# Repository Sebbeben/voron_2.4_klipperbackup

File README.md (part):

# voron_2.4_klipperbackup

Klipper configuration backup for my Voron 2.4 350 (pushed automatically by [Klipper-backup](https://github.com/Staubgeborener/Klipper-Backup)).

## Hardware
- [Fysetc Voron 2.4 kit 350](https://github.com/FYSETC/FYSETC-Voron-2) (shipped with Spider v1.1 and Omron SSR, i.e. [BOM](https://github.com/FYSETC/FYSETC-Voron-2/blob/main/BOM.md) rev 1.3 / R2 rev 1.0)
  - XY + Z motors: 6x [17HS19-2004S-C](https://github.com/FYSETC/FYSETC-MOTORS/tree/main/17HS19-2004S-C) (2.0 A), run at 0.8 A
  - Bed heater: 300x300 silicone AC heater, 750 W, with thermal fuse RH15A125
- [Fysetc Aluminium parts kit](https://github.com/FYSETC/FYSETC-VORON-2.4-R2-Pro/tree/main/2.4%20R2%20CNC%20V2.0/2.4%20R2%20CNC%20V2.0)
- Raspberry Pi 4B 8GB
  - [Waveshare RS485 CAN HAT](https://www.waveshare.com/wiki/RS485_CAN_HAT) (MCP2515 over SPI, `oscillator=12000000, interrupt=25, spimaxfrequency=10000000` in `/boot/config.txt`)
- [Fysetc Spider v1.1](https://github.com/FYSETC/FYSETC-SPIDER) (connected to the Pi over UART `/dev/ttyAMA0`)
  - [Fysetc TMC2209 v3.1](https://github.com/FYSETC/FYSETC-TMC2209) ([Silent2209](https://fysetc.github.io/Silent2209/))
  - [Fysetc Canbus Expander for Spider](https://github.com/FYSETC/FYSETC-SPIDER/blob/main/images/CANBUS.jpg)
- [Mellow SB2040 v1](https://mellow-3d.github.io/fly_sb2040_v1_general.html#fly-sb2040-v1-overview) (CAN, 1 Mbit) - [pin definitions](https://mellow-3d.github.io/fly_sb2040_v1_pins.html)
- Orbiter extruder (version to be verified - `rotation_distance: 4.637` is the Orbiter 2.0 value)
  - [FYSETC G36HSY4405-6D-1200 stepper motor](https://github.com/FYSETC/FYSETC-MOTORS/blob/main/G36HSY4405-6D-1200/G36HSY4405-6D-1200.pdf), run at 0.65 A
- [Rapido UHF Hotend](https://www.phaetus.com/products/rapido-hotend?variant=45122834465045) (v1, HF + UHF nozzles included)
  - Currently: temporary V6 0.4 mm nozzle; plan: HF nozzle back, then UHF with a new toolhead
- [BTT Pi Screen 5"](https://github.com/bigtreetech/BIGTREETECH-TouchScreenHardware/tree/master/BTT%20Pi%20TFT50%20V2.0%20Github/Hardware)
- [BIQU CNC Voron Tap V2](https://github.com/Chaoticlab/CNC-Tap-for-Voron/tree/master/STL/CNC_VORON_TAP_V2) on SB2040 `gpio28` (replaced the Chaotic Labs Tap V2.0 / OptoTap v2.1). 2026-11-17: `PROBE_ACCURACY` stddev 0.0009 mm, range 0.0038 mm; `z_offset` -0.896
- X rail upgraded to MGN12H (needed for CNC Tap V2); Y and Z still original MGN9 (no grease ports). Greased with Mobilux EP 2
- CNC Aluminium Idlers
- [Meanwell LRS-200-24 psu](https://meanwell-ps.com/products/lrs-200-24)
- [Voron Daylight on a stick XXL](https://github.com/VoronDesign/Voron-Hardware/tree/master/Daylight) (`output_pin daylight`, PB15)
- Pi Cam (OV5647, 1280x720 @ 15 fps via Crowsnest)
- USB camera YJXU502S (Realtek RTS58xx, 0edc:2050), 1920x1080 @ 15 fps, Crowsnest `[cam 2]` ustreamer port 8081, Mainsail "USB Cam". The on-board LED is not controllable over USB (do not write to the UVC extension unit)
- Voron 2.4 silicone nozzle brush at the rear of the bed - KOMB area X 60.5-93.5, Y 347.5-350.0, Z 3.5 (Y 350.5 touches the frame)
- [Nevermore Duo](https://github.com/nevermore3d) under the bed (M3 T-nuts in the bed extrusion), 2 blowers in parallel on Spider FAN0 (`PB0`) as `[fan_generic nevermore]`. On in `PRINT_START` when bed > 90 C, off 10 min after `PRINT_END`
- ADXL345 accelerometer (loose, mounted on the toolhead only for calibration) wired to the Pi SPI0 bus, **CS on CE1 = pin 26 / GPIO7** (CE0 = pin 24 belongs to the MCP2515 CAN HAT - CS there kills CAN). Pi runs `klipper-mcu` as `[mcu rpi]`, `[adxl345] spi_bus: spidev0.1`, `axes_map: -z,-y,-x`
- Chamber air: 3 x NTC 100K (temporary test positions, Spider TE0/TE1/TE2 = PC0/PC1/PC2), `chamber_sensors.cfg`. Z `position_max` temporarily 200 while they hang under the top panel (restore 340)
- Gantry NTC (2026-11-25): a 4th NTC 100K pulled through the Z drag chain together with the new A/B motor cables, **not connected yet**. Plan: chamber air sensor on top of the gantry extrusion (moves with Z, so it reads the air at the gantry, which is what drives QGL/gantry drift). All Spider thermistor inputs are taken (PC0/PC1/PC2 chamber, PC3 bed), so it replaces one of the test sensors (`chamber_side` PC1 is the obvious one). Mounting: middle of the gantry, >= 100 mm from the A/B motors (they warm the aluminium), bead 10-20 mm above the extrusion in free air, not touching metal (printed standoff), outside the part-fan / Nevermore airflow. Expect it to read high at low Z (bed radiation) - only trust it for heatsoak at print height
- [OMRON G3NB-225B-1 25A SSR](https://www.omron-ap.com/products/family/3232/download/catalog.html)

### Fans
| Position | Fan | Pin | Status |
|---|---|---|---|
| Hotend (lower, 4010 axial) | [HoneyBadger 4010A-24-9400 "High SP & Tach"](https://3do.dk/en/fans/1145-4010-axial-fan-24v-by-honeybadger-high-sp-9400-rpm.html), 3-wire, not PWM | SB2040 fan adapter "Hotend Fan1": red -> 24V, black -> AGND (switched GND, `gpio14`); white tach **not connected** yet | **Installed 2026-11-17**, tested: on at 50 C, off below 50 C |
| Part cooling (upper, 5015 blower) | [HoneyBadger 5015 blower 9200 RPM, 4-wire PWM/tach, wide mouth](https://3do.dk/en/fans/4366-5015-blower-fan-by-honeybadger-9200-rpm-4-wires-pwmtach-wide-mouth.html) | SB2040 power `gpio13`, PWM `gpio17` | Ordered 2026-11-13 - duct needs adapting for the wide mouth |
| Electronics bay | Kit 6020 fans | Spider `PB2` (on when bed > 45 C) | Check that they still spin |
| Nevermore Duo | 2 x blower | Spider FAN0 `PB0` | Installed 2026-11-17 |

Hotend fan config: `printer.cfg` `[heater_fan hotend_fan]` (wiring in the comments). Stall watchdog: `hotend_fan_alarm.cfg` (included, idle until the tach is wired; plan 2026-11-25: tach -> SB2040 ENDSTOP_2 `gpio25`).

**Hotend fan wiring notes (learned the hard way, 2026-11-17):**
- On the Mellow fan adapter, "AGND" is the *switched* fan ground (low-side MOSFET), not analog ground. 2-wire / non-PWM fans go 24V + AGND.
- The adapter's "3 Line: S = PWM" row is for PWM fans only. A tach wire must **never** go to PWM0/PWM1: with the white tach on PWM0 (`gpio16`) the SB2040 MCU temperature read 120-135 C and Klipper shut down.
- The adapter has no tach input. SB2040 v1 inputs (schematic REV 1.0): ENDSTOP_0 `gpio28` (JP9, 4.7k pull-up to 3V3, Tap), ENDSTOP_1 `gpio29` (JP10, 4.7k pull-up, reserved for the X endstop), ENDSTOP_2 `gpio25` (JP11: 1 = signal, 2 = GND, 3 = **24 V**; input through a 1N4148 cathode-to-connector + 1k, 100 nF on the connector side, no pull-up -> 24 V tolerant, pulls low only). Status LED is `gpio24`, not 25.
- Tach plan: white wire -> JP11 pin 1, nothing on pin 3, `tachometer_pin: ^SB2040:gpio25`. First measure the white wire with the fan running and unconnected: if it shows a voltage the fan has its own pull-up and it works directly; if ~0 V add a 10k pull-up from the tach line to JP11 pin 3 (24 V), because the 100 nF + internal ~50k pull-up through the diode is too slow for ~310 Hz.

The part fan (5015) config is still prepared (commented out) in `fan_upgrade.cfg`.

## Hardware *Not installed*
- Mellow 3 m shielded twisted-pair CAN cable (20CANW3M) - plan: replace the current CAN cable
- FYSETC belt tension gauge (tool)
- Spare Orbiter motor: FYSETC 36STH20-1004AHG
- Simple filament runout switch
- Voron PT100 Stick
- Fysetc CNC Aluminium Clockwork extruder
- Unused kit parts: BMG extruder kit + 42HS20401B motor, E3D V6 hotend

## Klipper Mods
- [Klipper-backup](https://github.com/Staubgeborener/Klipper-Backup)
- [Klipper-Adaptive-Meshing-Purging (KAMP)](https://github.com/kyleisah/Klipper-Adaptive-Meshing-Purging) - Smart_Park is used in `PRINT_START`
- [KOMB](https://github.com/TmRxJD/KOMB) nozzle brushing macro - **enabled 2026-11-17**. Local patch in `KOMB/KOMB.cfg`: travel to the brush at z_hop height *before* lowering (upstream lowers first and crosses the bed at brush height)
- [Filament dryer macro](https://gist.github.com/NameOfTheDragon/e579295549aaa19b3f41ae07b8f3cbd6#file-filament_dryer-cfg) - `DRY_ABS` = bed 95 C for 5 h (spool on a spacer, door slightly open)
- Crowsnest, Moonraker-timelapse, Sonar, KlipperScreen

## Printed Mods
- [Orbitu for Stealthburner Orbiter extruder](https://github.com/Saccco/VoronUsers/tree/master/printer_mods/Saccco/Orbitu)
- Planned: [Voron Stealthburner Rapido UHF](https://www.printables.com/model/1272320-voron-stealthburner-rapido-uhf) (4010 hotend fan version)

## Maintenance log

### 2026-11-27 - extruder grip fixed, R3D ABS calibrated, USB cam CPU lowered
- Max-flow walls failed at ~15 mm3/s -> in-air feed test (100 mm per step, tape mark): Orbiter tension far too loose (16 mm3/s fed 88 %, 20 fed 77 %). Tightened in quarter turns: 20 -> 97 %, 24 -> 94 %, 28 -> motor skips at 250 C, 88 % without skipping at 260 C
- `rotation_distance` 4.544 -> **4.703** (4.544 fed 103.5 mm after the tension fix; re-check fed exactly 100 mm)
- Second calibration plate (all tests on one plate, `plate_20261127.gcode`), judged with a microscope: flow ratio **0.99**, PA **0.045** kept, **250 C**, retraction **0.5 mm**, max volumetric **18 mm3/s** (22 at 260 C). Values in `orca_profiles/ABS @...json` + `orca_profiles/README.md`; best photos in `~/calibration/` on the Pi
- Remaining fine wisps on travel are the same at 0.4 and 1.2 mm retraction -> dry the filament (`DRY_ABS`)
- USB cam WebRTC (go2rtc, with audio) encode 960x540 @ 15 -> 640x360 @ 10 fps: encoder ~78 % -> ~44 % of a core while watched. Full-res snapshot unchanged

### 2026-11-18 - A/B motor fault hunt, motors ordered, camera sound in Mainsail
- Sensorless homing `uv_cp` fault traced step by step to **motor B** (supply, driver modules, X-MOT socket, both cables and endstop ports ruled out - details in TODO "A/B motor fault"). Motor A cable was also bad (open-load flags) and was replaced
- `homing_v2.cfg`: `G4 P2000` before sensorless `G28 X`/`G28 Y` (Klipper TMC docs); X/Y `homing_speed` back to 80
- Ordered 2 x LDO-42STH48-2504AC + 2 x adhesive heatsinks (3do.dk). Printer parked until they arrive; X-MOT/Y-MOT plugs and pins are temporarily swapped
- Driver/motor research: Spider v1.1 is 24 V only (35 V caps); TMC2240 (SPI, StallGuard4) is the next driver step; LDO "Super Power" 2804 only pays off with 48 V; no vibration dampers on A/B
- Chamber heater research (PTC 300-500 W, ~80 C practical limit, PA/PC possible, PEEK/PEI not) - TODO "Chamber heater"
- USB camera sound: go2rtc v1.9.14 installed as a service, nginx proxy `/go2rtc/`, Mainsail webcam "USB Cam + ljud" (WebRTC go2rtc, audio). Video via software x264 960x540 (the Pi hardware encoder only sent SPS/PPS once). Mic gain +12 dB (saved). Mainsail player patched (`printer_data/config/system/mainsail_go2rtc_audio_patch.sh`, re-run after Mainsail updates) - Mainsail kept re-muting the video and had no controls. Old MJPEG "USB Cam" entry removed. Sound verified on another PC (not yet on the main PC - local browser/PC issue)
- Camera LED: still no software control found (only Realtek raw-register XU 4, not touched). Connector has 5 pins - the extra pin is the next thing to check; seller asked

### 2026-11-17 - On site: homing, Tap, brush, Nevermore, input shaper, hotend fan
- `G28 X` shut down with `TMC stepper_x GSTAT uv_cp=1` (charge-pump undervoltage). Homing "finished" instantly (driver fault raises DIAG = fake stall). **Cause: loose 24 V cable** - re-tightened, homing fine since. If `uv_cp` comes back, check the 24 V terminals first.
- `homing_v2.cfg` enabled (fixed `SET_KINEMATIC_POSITION` defaulting to `SET_HOMED=xyz`), X/Y `homing_speed` 80 -> 40.
- CNC Tap V2: QGL converges in 2-3 retries, `PROBE_ACCURACY` stddev 0.0009 mm. `z_offset` -0.896 (paper test, cold nozzle, old value -0.810).
- KOMB brush measured and enabled (see Hardware).
- Nevermore Duo installed and configured.
- ADXL345 on the Pi + `klipper-mcu`; input shaper saved: **X `2hump_ei` 92 Hz, Y `mzv` 52.8 Hz**. X shows two broad peaks (~57 Hz and 115-135+ Hz, test stops at 135 Hz) -> toolhead not rigid yet (SB2040 only taped, ADXL ~16 deg tilted). Redo after the toolhead is finished with `SHAPER_CALIBRATE AXIS=X FREQ_END=170`. Graphs + raw data: `printer_data/config/shaper_graphs/` (rendered with `~/shaper-env`, a separate venv with matplotlib).
- Hotend fan HoneyBadger 4010 installed (see Fans), tach not wired yet.

### 2026-11-13 - Clog investigation
Symptom: clogs high up in the hotend, appearing "after a while", not at the same point every time.

Findings:
- **Root cause: the hotend fan was dead.** Cheap 2-wire sleeve-bearing 4010 (CAIZHU). 24 V measured at the fan with the port on, fan does not spin. Sleeve bearings wear out quickly in a ~60 C chamber, so the fan most likely slowed down over time, causing heat creep.
- Orbiter drive gears were packed with ground filament (extruder slipping against the blockage).
- Burnt ABS in the Rapido core and charred specks on the ceramic: leak between nozzle and heatbreak. Hot-tighten the nozzle at 250 C.
- Config history: `pressure_advance` was 0.3546 (10x too high) from 2025-06-17 to 2025-06-25. That week had ~15 failed prints and probably started the heatbreak contamination.
- Heatbreak cleaned with cold pulls; no clear evidence of scratches.
- Cura asks for up to ~22 mm3/s (p90) at 240 C with 300 mm/s infill, which is too much for this setup.

Config changes (backup of the old files kept locally):
- Extruder `run_current` 0.5 -> 0.65
- `PRINT_END` retract 5 mm -> 1.5 mm
- `UNLOAD_FILAMENT` now forms a tip before pulling out
- `DRY_ABS` bed 65 C / 4 h -> 95 C / 5 h
- Removed duplicate `sensor_type` in `[temperature_sensor RPi_4B]`
- Added `fan_upgrade.cfg` (inactive)

## TODO
- **New filament calibration (CALIB_PLATE, 2026-11-27):** `CALIB_PLATE MATERIAL=PETG RESET=1` (ABS PLA PETG TPU NYLON POM; `LIST=1`, `TEMP=0`, `NOZZLE=`, `BED=`, `NAME=`) writes `calib_<MAT>_<date>.gcode`: flow tiles, PA lines, bridges 10-50 mm (`BRIDGE=0` skips), retraction, max flow and the temp tower last, each one connected piece on a one-layer web with raised values and a title. Generic start values in `tools/calib_plate.py` - check against the spool. Active after the next Klipper restart (include added while a print was running). Next week: PETG, PLA, TPU, nylon, POM.
- **Belt panel on real belts:** try the new views (one belt per screen, sketches, auto-move, guided A/B), check B=left / A=right and the "fixed" Z side in the sketches, and whether the signal meter (Signal/noise) and tips match how plucking feels. Measure the Z height for a 150 mm Z span once and press Save Z.
- **Pi temperature:** 81-83 C and throttling with both camera streams + WebRTC viewers (Orca device tab, Edge). USB cam WebRTC lowered 2026-11-27; the Pi cam (camera-streamer, 1296x972 @ 15, ~80-90 % of a core) is now the biggest load - lower its fps and/or add Pi cooling.
- **Calibration plate cleared:** run `python3 tools/gen_flow_tiles.py --reset-layout` before generating new tests.
- **Klipper local patch:** `klippy/mcu.py` TRSYNC_TIMEOUT 0.025 -> 0.050 (2026-11-26, Tap over CAN timed out during homing). Reapply after every Klipper update.
Status 2026-11-18: **printer parked** until new A/B motors arrive. Sensorless X/Y homing fails with TMC `uv_cp` (Undervoltage) - traced to the **motor B (stepper_x)**, see "A/B motor fault" below. Do not print until the motors are replaced.

### Done 2026-11-13
- [x] Klipper CPU pinning fixed (`[Service]` header) - Klipper runs on core 3
- [x] MCP2515 SPI clock 2 MHz -> 10 MHz in `/boot/config.txt` - after reboot: 0 `rx_over_errors` (was ~240-310/h at 2 MHz)
- [x] Software updated: Klipper v0.13.0-827, Moonraker v0.11, Mainsail v2.19, Crowsnest v4.2, klipper-backup, Sonar, KAMP (MCU firmware still v0.13.0-112/120 - works)
- [x] Adaptive mesh verified: already active via KAMP (`exclude_object` + Moonraker object processing)
- [x] KOMB include path fixed (still commented out), duplicate `KOMB.cfg` removed
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
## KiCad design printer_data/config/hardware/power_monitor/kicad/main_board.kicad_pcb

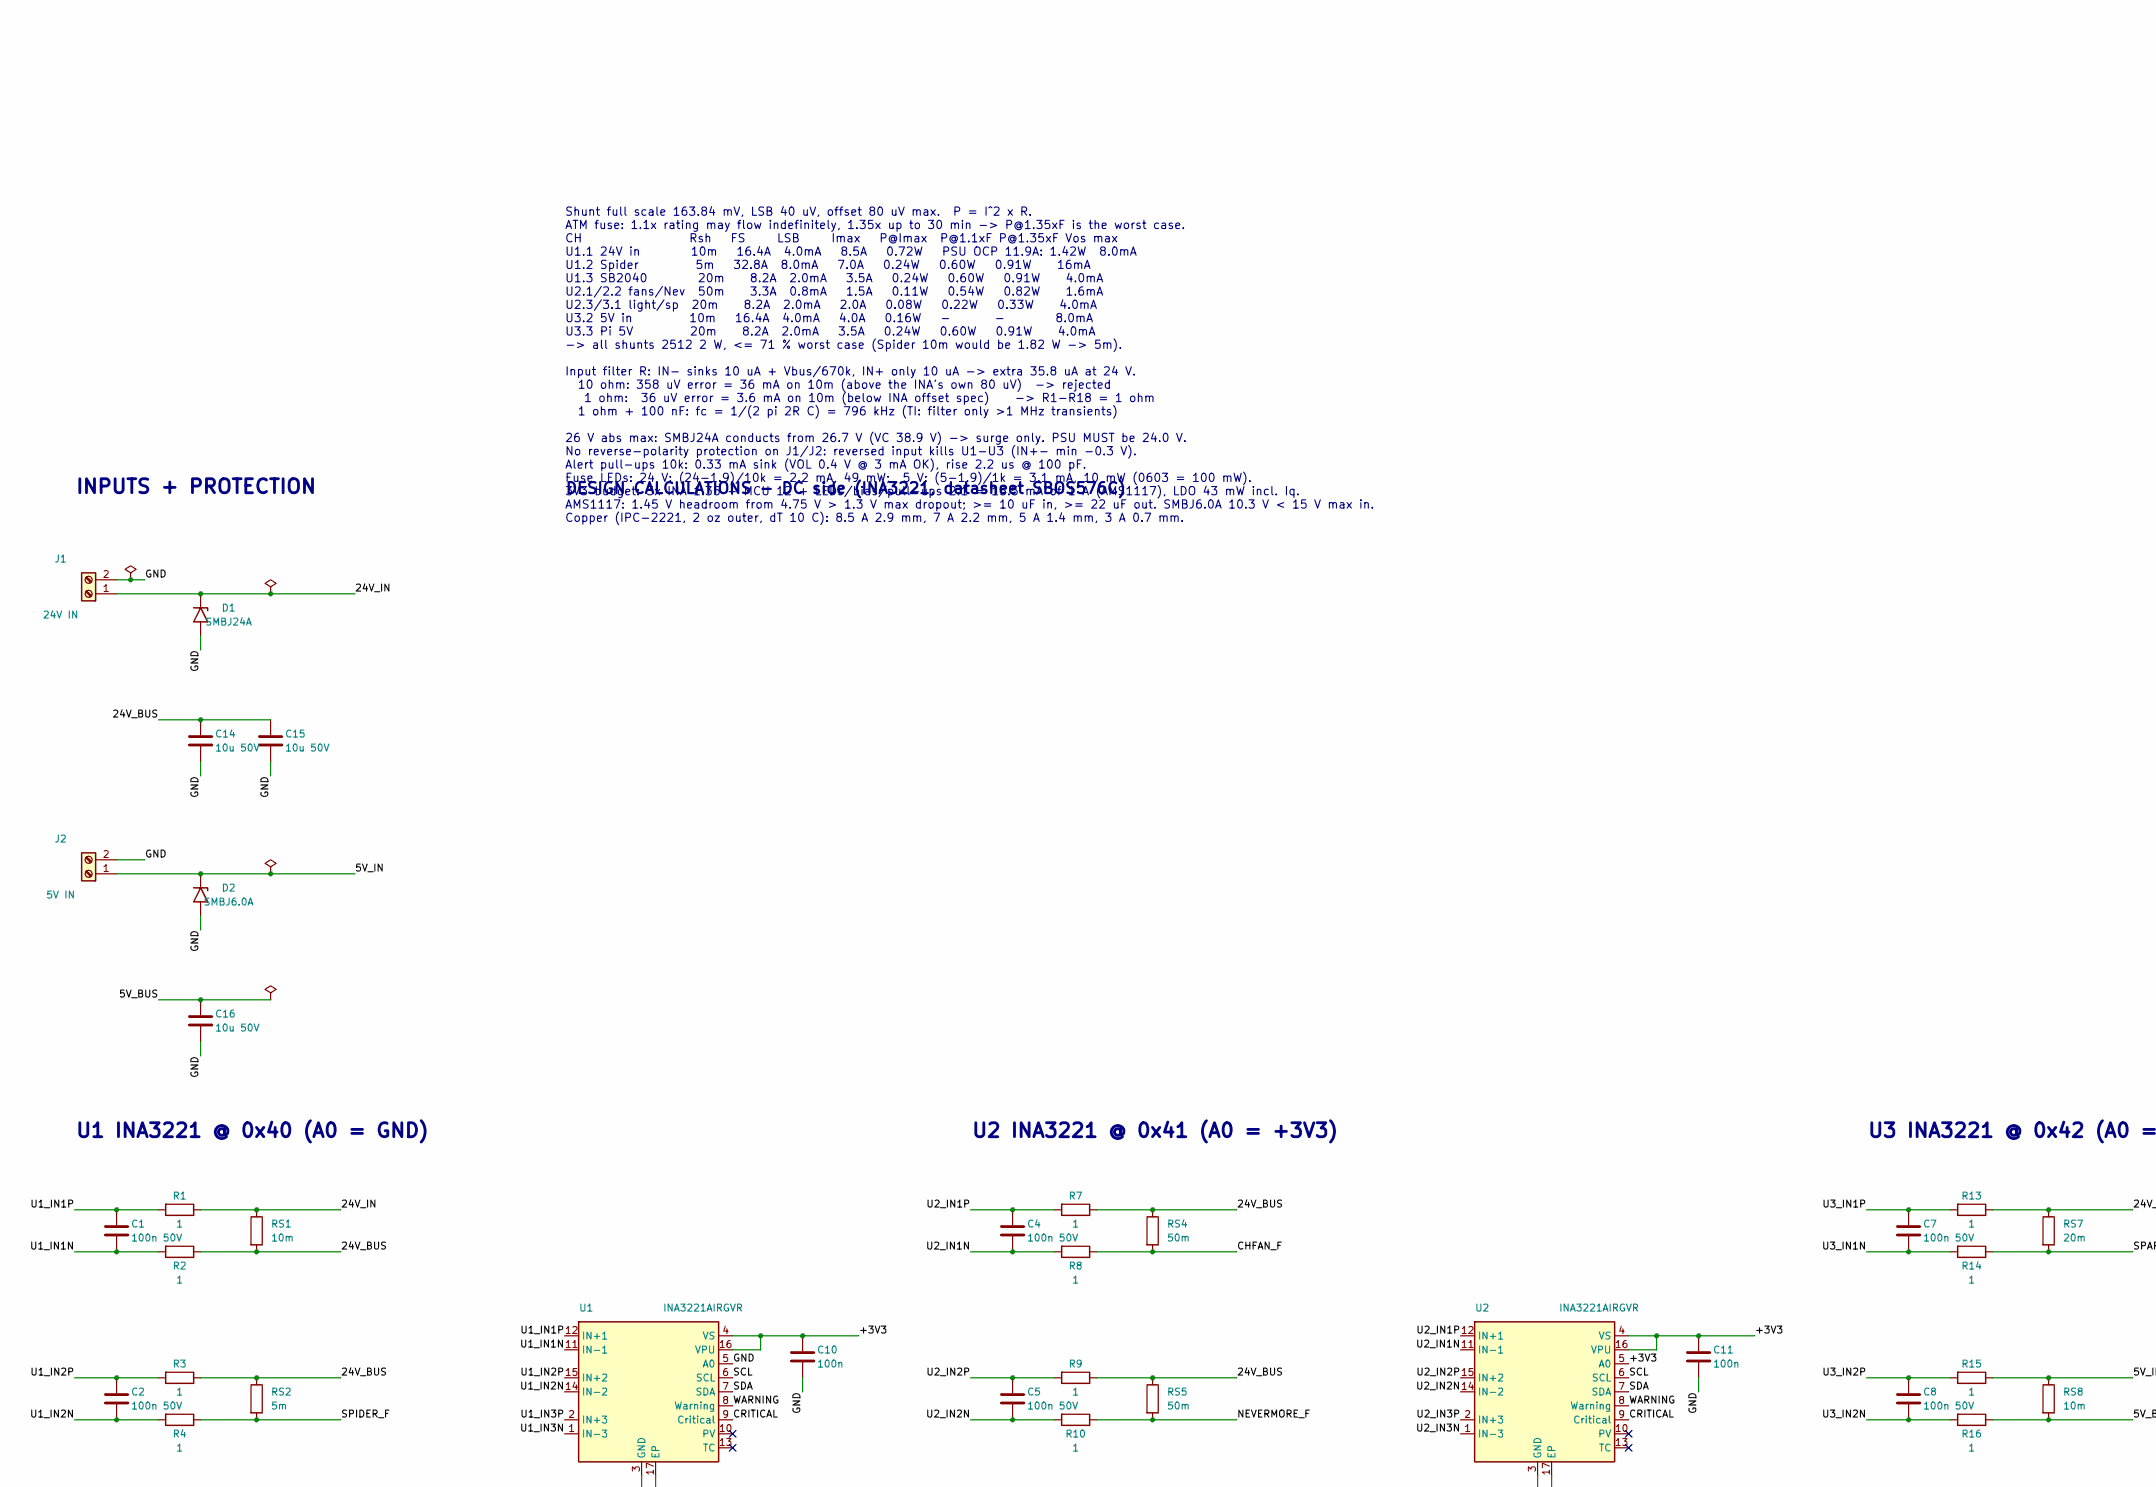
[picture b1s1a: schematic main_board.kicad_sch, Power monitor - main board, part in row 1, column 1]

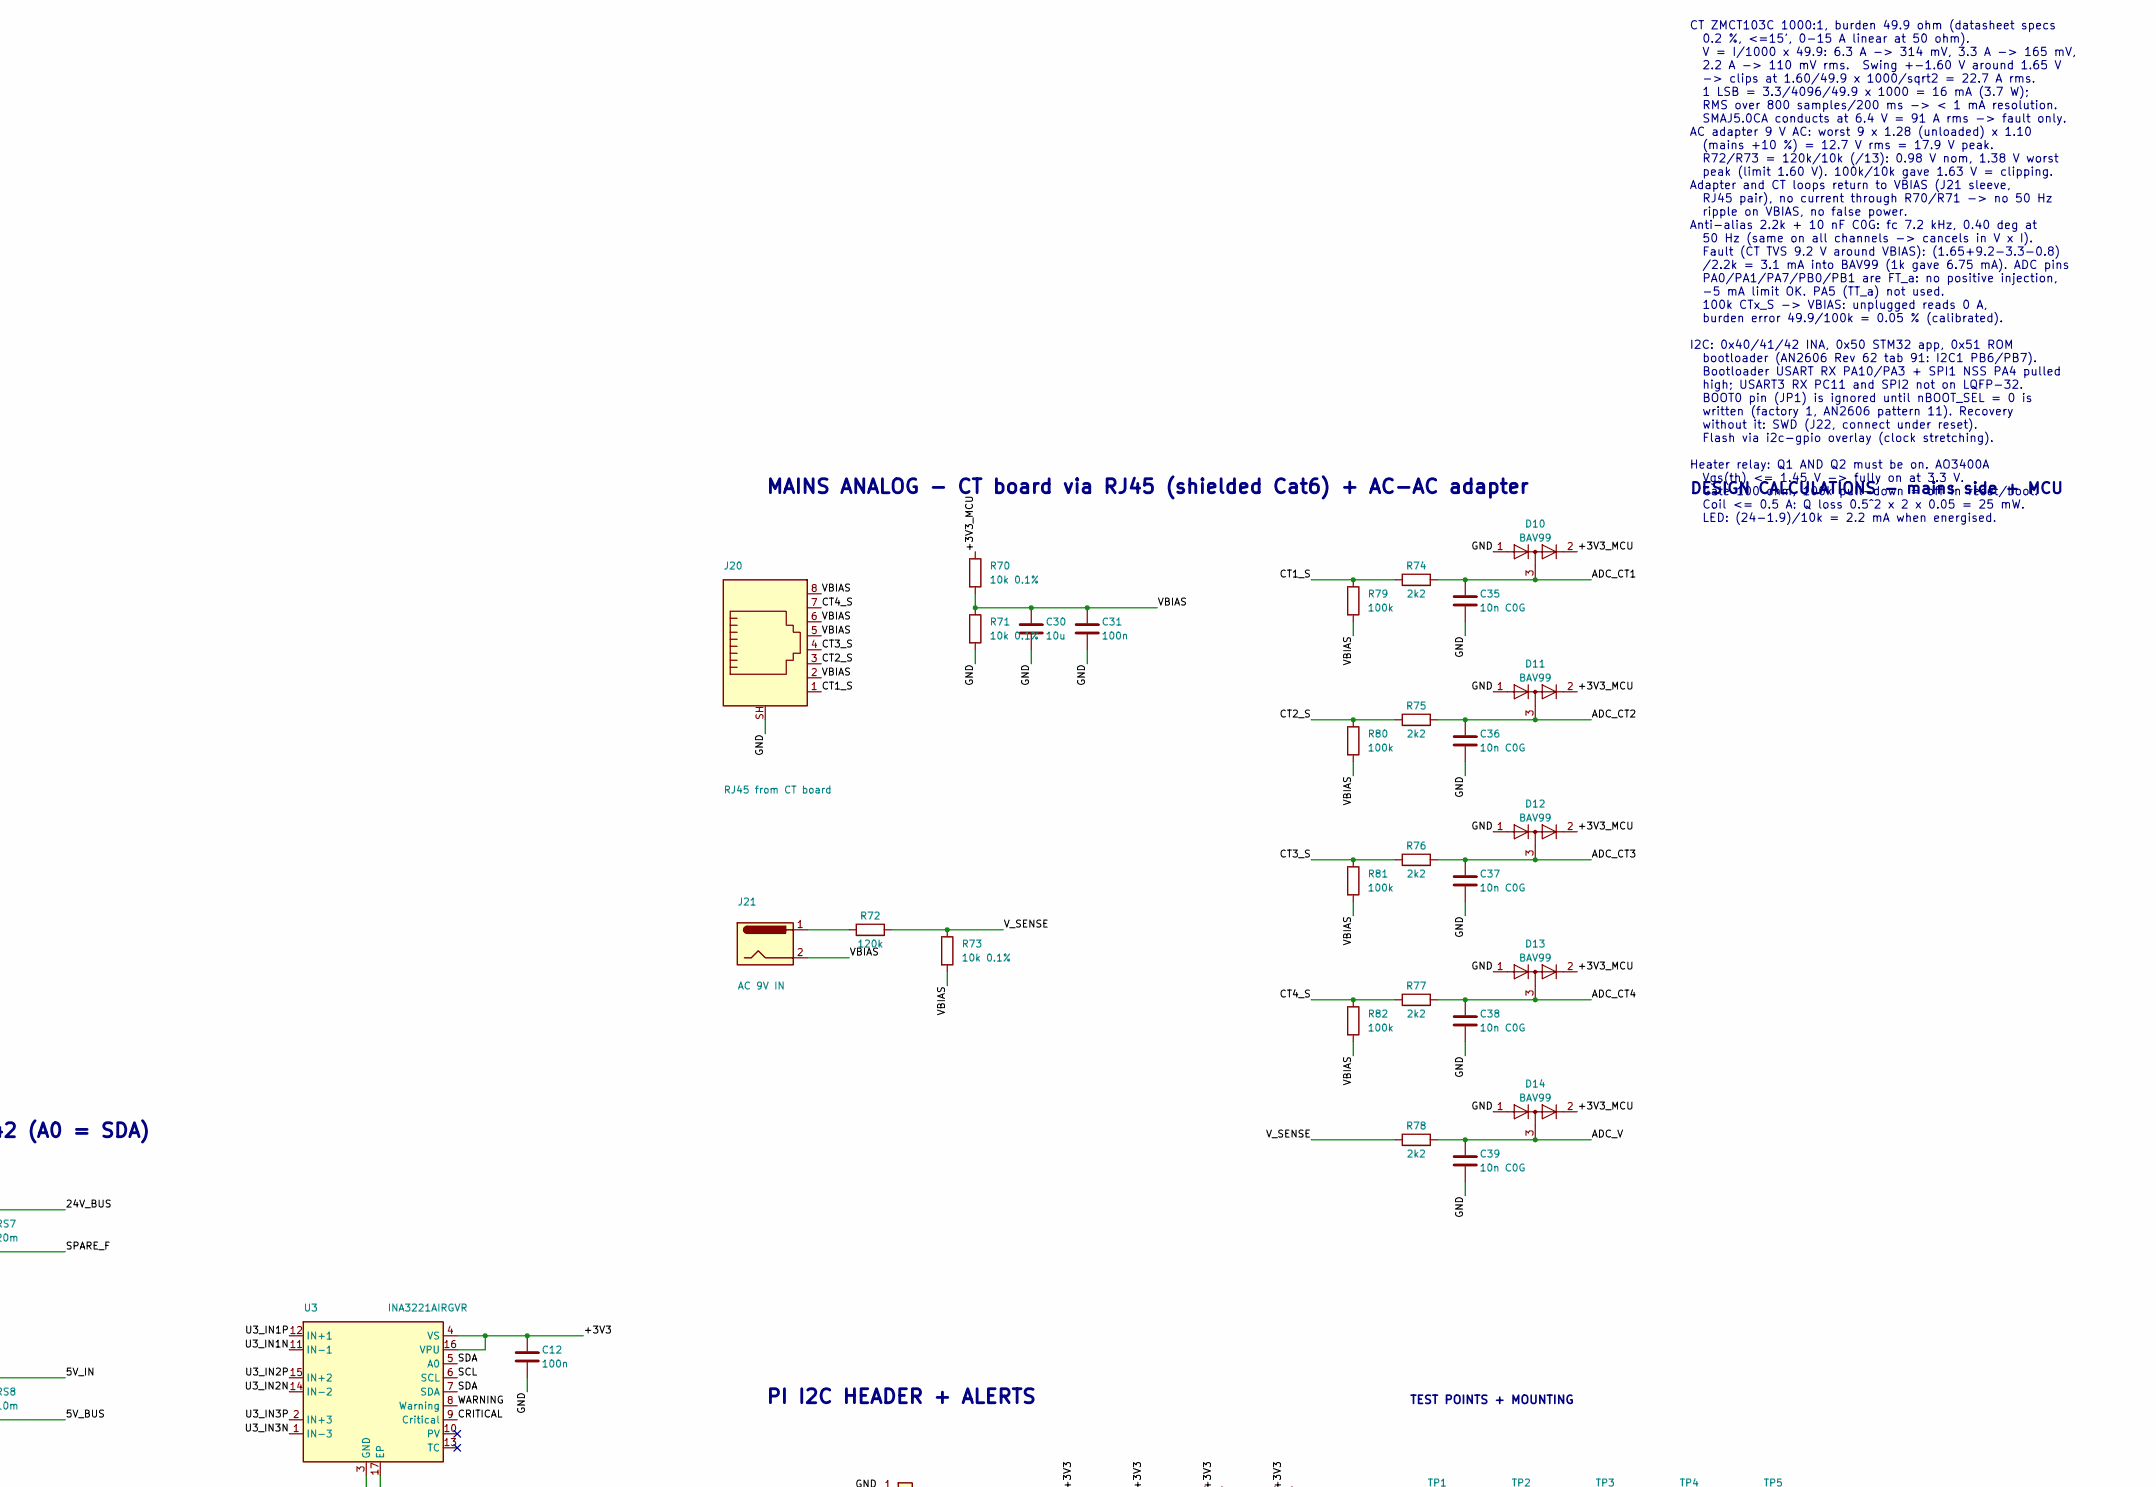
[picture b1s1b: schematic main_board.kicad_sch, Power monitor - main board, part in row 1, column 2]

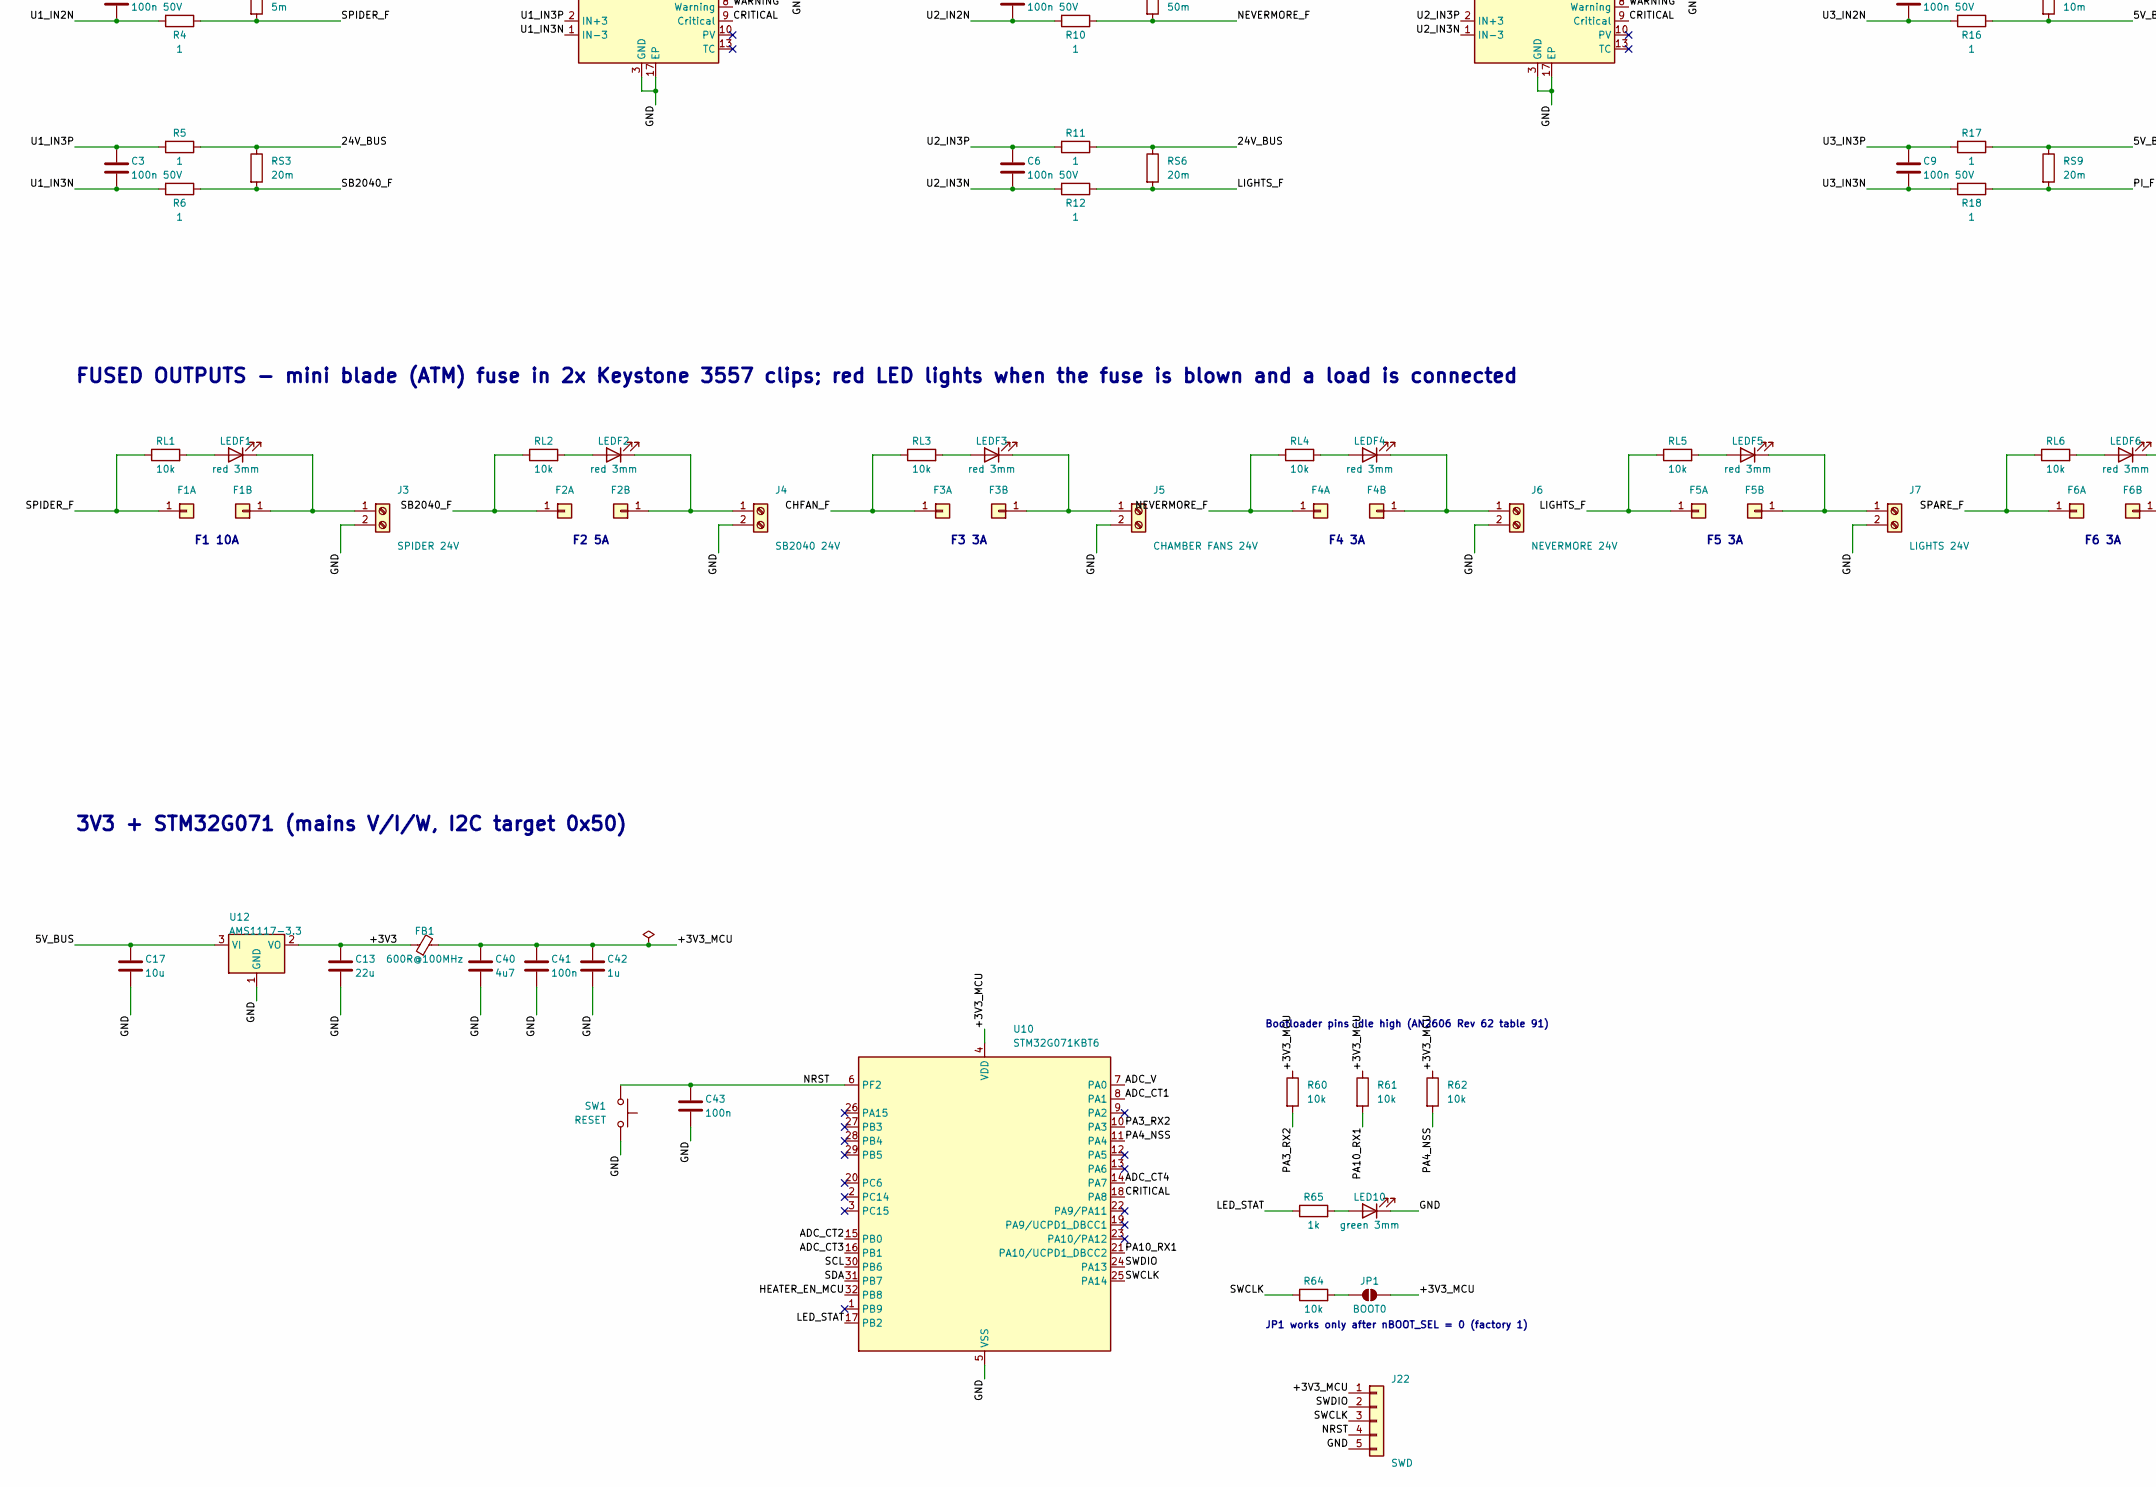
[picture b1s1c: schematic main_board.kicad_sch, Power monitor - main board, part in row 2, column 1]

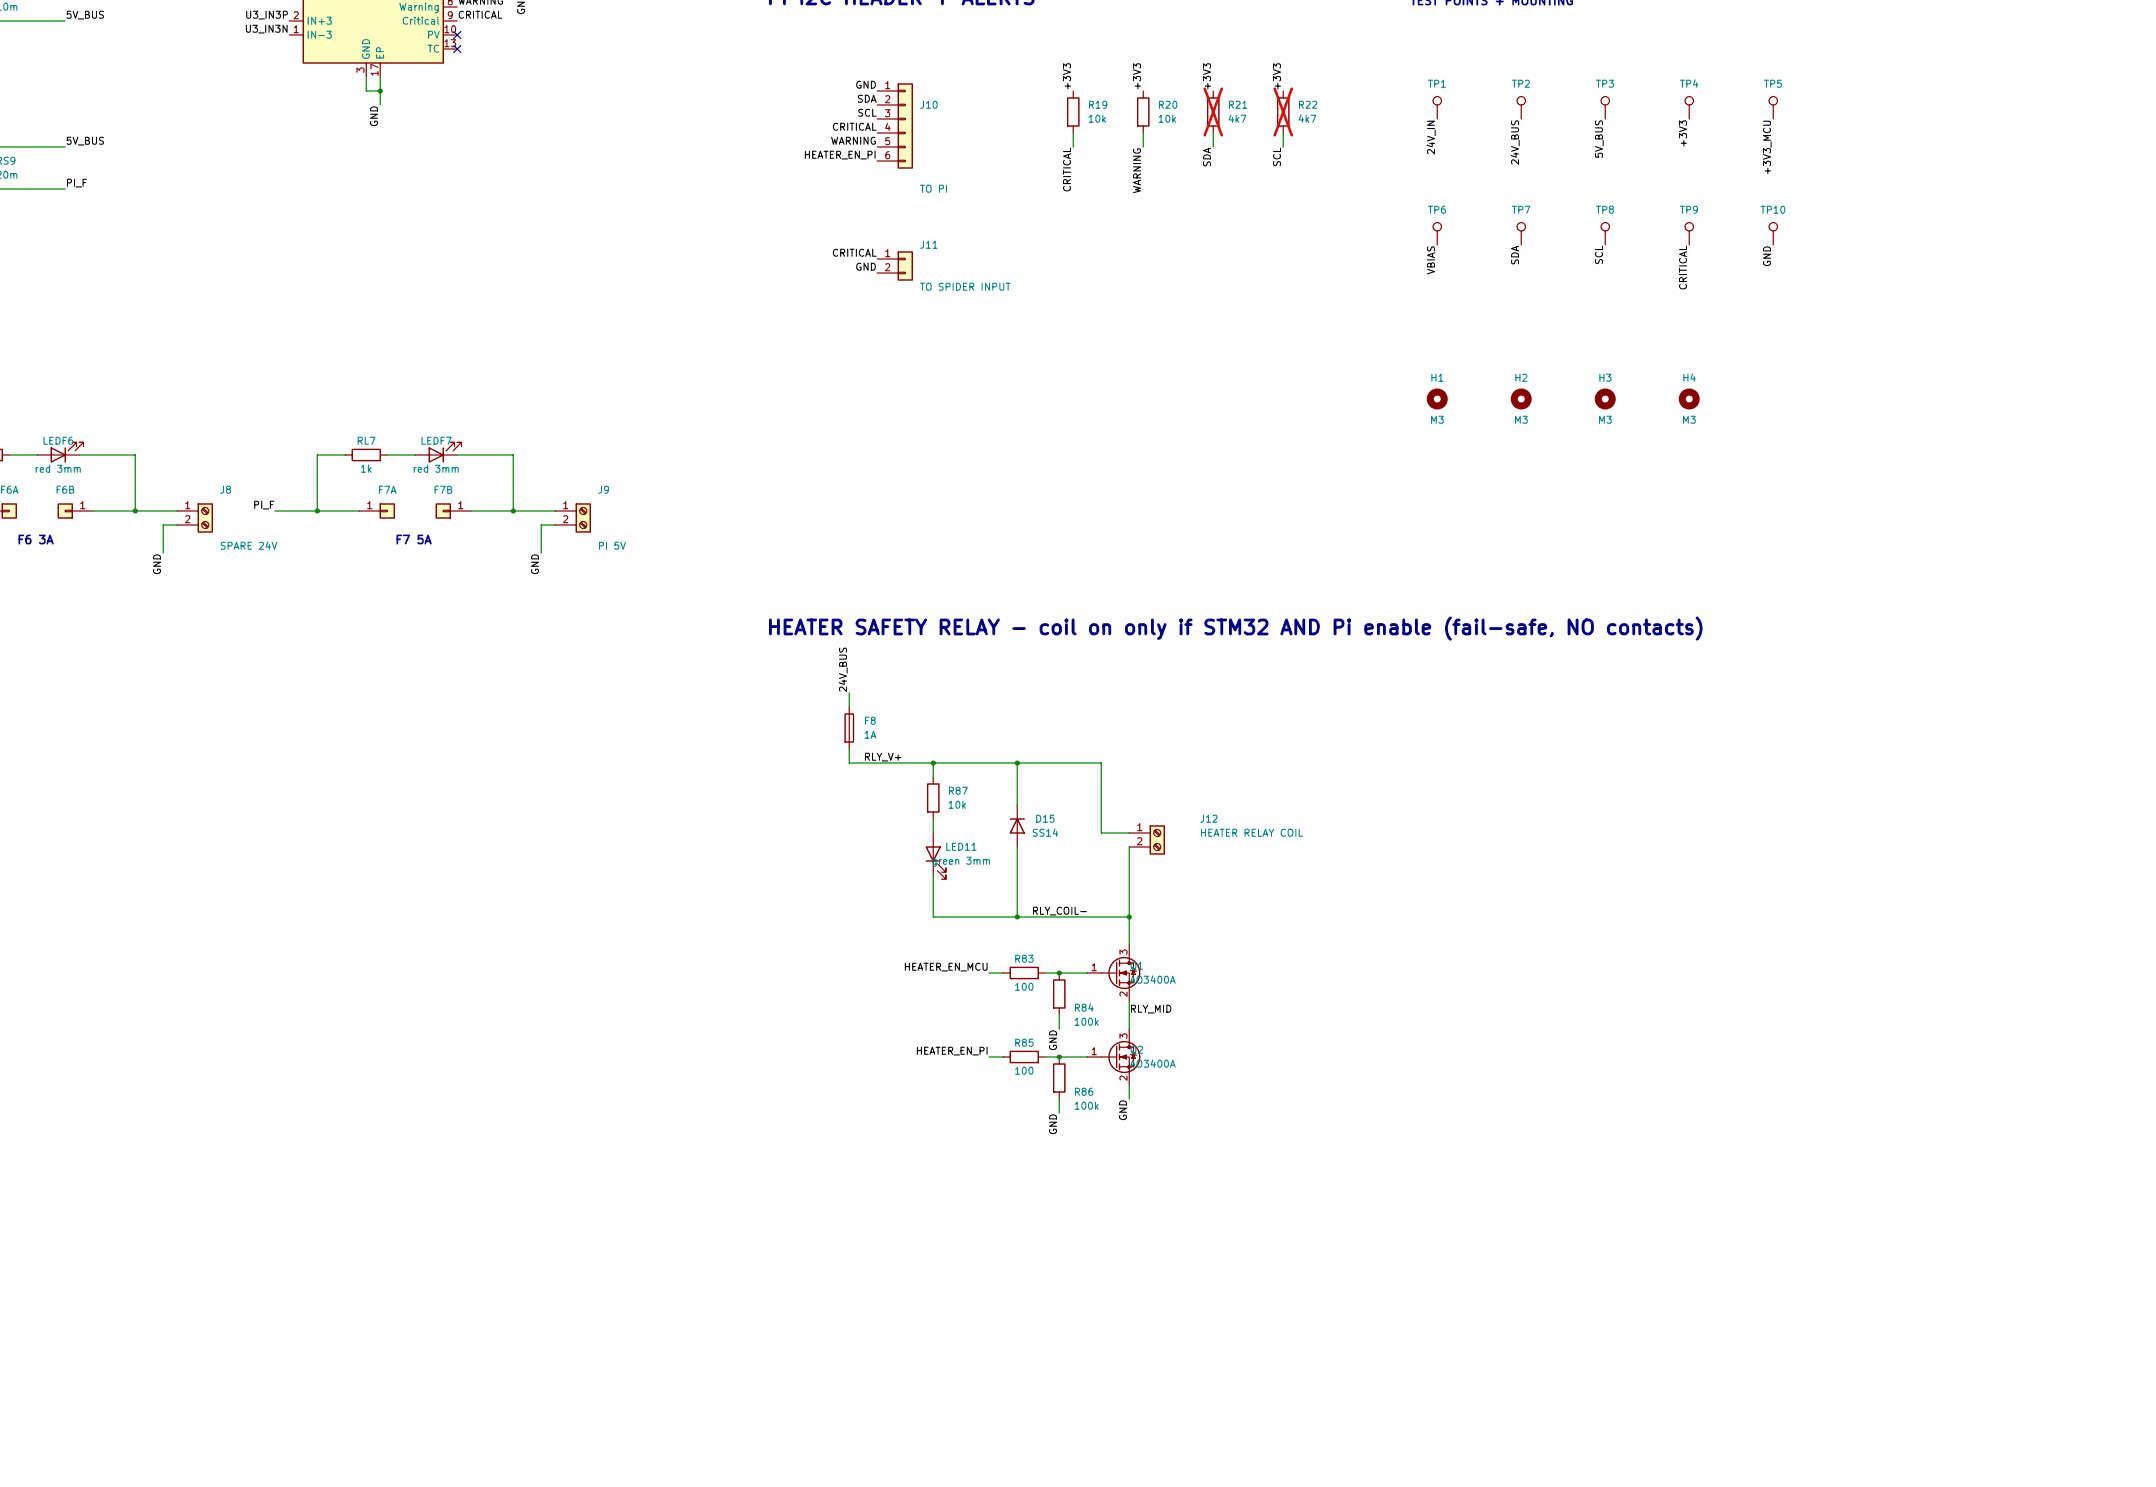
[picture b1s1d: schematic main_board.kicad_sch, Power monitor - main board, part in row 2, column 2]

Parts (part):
C1, C2, C3, C4, C5, C6, C7, C8, C9: 100n 50V; C_0603_1608Metric; MPN YAGEO CC0603KRX7R9BB104; LCSC C14663
C10, C11, C12, C31, C41, C43: 100n; C_0603_1608Metric; MPN YAGEO CC0603KRX7R9BB104; LCSC C14663
C13: 22u; C_0805_2012Metric; MPN Samsung CL21A226MAQNNNE; LCSC C45783
C14, C15, C16: 10u 50V; C_1206_3216Metric; MPN Samsung CL31A106KBHNNNE; LCSC C13585
C17, C30: 10u; C_0805_2012Metric; MPN Samsung CL21A106KAYNNNE; LCSC C15850
C35, C36, C37, C38, C39: 10n C0G; C_0603_1608Metric; MPN TDK C1608C0G1H103JT000N; LCSC C76599
C40: 4u7; C_0805_2012Metric; MPN Samsung CL21A475KAQNNNE; LCSC C1779
C42: 1u; C_0805_2012Metric; MPN Samsung CL21B105KBFNNNE; LCSC C28323
D1: SMBJ24A; D_SMB; MPN Littelfuse SMBJ24A; LCSC C224017
D2: SMBJ6.0A; D_SMB; MPN MDD SMBJ6.0A; LCSC C113976
D10, D11, D12, D13, D14: BAV99; SOT-23; MPN Nexperia BAV99,215; LCSC C2500
D15: SS14; D_SMA; MPN MDD SS14; LCSC C2480
F1A, F1B: CLIP F1 10A; Fuseclip_Blade_Mini_Keystone_3557; MPN Keystone 3557; LCSC C2680614
F2A, F2B: CLIP F2 5A; Fuseclip_Blade_Mini_Keystone_3557; MPN Keystone 3557; LCSC C2680614
F3A, F3B: CLIP F3 3A; Fuseclip_Blade_Mini_Keystone_3557; MPN Keystone 3557; LCSC C2680614
F4A, F4B: CLIP F4 3A; Fuseclip_Blade_Mini_Keystone_3557; MPN Keystone 3557; LCSC C2680614
F5A, F5B: CLIP F5 3A; Fuseclip_Blade_Mini_Keystone_3557; MPN Keystone 3557; LCSC C2680614
F6A, F6B: CLIP F6 3A; Fuseclip_Blade_Mini_Keystone_3557; MPN Keystone 3557; LCSC C2680614
F7A, F7B: CLIP F7 5A; Fuseclip_Blade_Mini_Keystone_3557; MPN Keystone 3557; LCSC C2680614
F8: 1A; Fuse_1206_3216Metric; MPN Littelfuse 0466001.NRHF; LCSC C151135
FB1: 600R@100MHz; L_0603_1608Metric; MPN Murata BLM18KG601SN1D; LCSC C85833
H1, H2, H3, H4: M3; MountingHole_3.2mm_M3
J1: 24V IN; TerminalBlock_Phoenix_MKDS-1,5-2-5.08_1x02_P5.08mm_Horizont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; MPN Kangnex WJ500V-5.08-2P; LCSC C8465
J2: 5V IN; TerminalBlock_Phoenix_MKDS-1,5-2-5.08_1x02_P5.08mm_Horizont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; MPN Kangnex WJ500V-5.08-2P; LCSC C8465
J3: SPIDER 24V; TerminalBlock_Phoenix_MKDS-1,5-2-5.08_1x02_P5.08mm_Horizont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; MPN Kangnex WJ500V-5.08-2P; LCSC C8465
J4: SB2040 24V; TerminalBlock_Phoenix_MKDS-1,5-2-5.08_1x02_P5.08mm_Horizont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; MPN Kangnex WJ500V-5.08-2P; LCSC C8465
J5: CHAMBER FANS 24V; TerminalBlock_Phoenix_MKDS-1,5-2-5.08_1x02_P5.08mm_Horizont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; MPN Kangnex WJ500V-5.08-2P; LCSC C8465
J6: NEVERMORE 24V; TerminalBlock_Phoenix_MKDS-1,5-2-5.08_1x02_P5.08mm_Horizont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; MPN Kangnex WJ500V-5.08-2P; LCSC C8465
J7: LIGHTS 24V; TerminalBlock_Phoenix_MKDS-1,5-2-5.08_1x02_P5.08mm_Horizont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; MPN Kangnex WJ500V-5.08-2P; LCSC C8465
J8: SPARE 24V; TerminalBlock_Phoenix_MKDS-1,5-2-5.08_1x02_P5.08mm_Horizont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; MPN Kangnex WJ500V-5.08-2P; LCSC C8465
J9: PI 5V; TerminalBlock_Phoenix_MKDS-1,5-2-5.08_1x02_P5.08mm_Horizont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; MPN Kangnex WJ500V-5.08-2P; LCSC C8465
J10: TO PI; JST_XH_B6B-XH-A_1x06_P2.50mm_Vertical; MPN JST B6B-XH-A(LF)(SN); LCSC C144397
J11: TO SPIDER INPUT; JST_XH_B2B-XH-A_1x02_P2.50mm_Vertical; MPN JST B2B-XH-A(LF)(SN); LCSC C158012
J12: HEATER RELAY COIL; TerminalBlock_Phoenix_MKDS-1,5-2-5.08_1x02_P5.08mm_Horizont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; MPN Kangnex WJ500V-5.08-2P; LCSC C8465
J20: RJ45 from CT board; RJ45_Kinghelm_KH-RJ45-58_Shielded_Horizontal; MPN kinghelm KH-RJ45-58-8P8C; LCSC C2683360
J21: AC 9V IN; BarrelJack_Horizontal; MPN CUI PJ-002AH; LCSC C2961147
J22: SWD; PinHeader_1x05_P2.54mm_Vertical
JP1: BOOT0; SolderJumper-2_P1.3mm_Open_RoundedPad1.0x1.5mm
LED10, LED11: green 3mm; LED_D3.0mm; MPN Everlight 204-10SYGD/S530-E2-L; LCSC C181864
LEDF1, LEDF2, LEDF3, LEDF4, LEDF5, LEDF6, LEDF7: red 3mm; LED_D3.0mm; MPN Everlight 204-10SURD/S530-A3-L; LCSC C99771
Q1, Q2: AO3400A; SOT-23; MPN AOS AO3400A; LCSC C20917
R1, R2, R3, R4, R5, R6, R7, R8, R9, R10, R11, R12, R13, R14, R15, R16, R17, R18: 1; R_0603_1608Metric; MPN UNI-ROYAL 0603WAF100KT5E; LCSC C22936
R19, R20, R60, R61, R62, R64, R87: 10k; R_0603_1608Metric; MPN UNI-ROYAL 0603WAF1002T5E; LCSC C25804
R21, R22: 4k7; R_0603_1608Metric; MPN UNI-ROYAL 0603WAF4701T5E; LCSC C23162; not fitted
R65: 1k; R_0603_1608Metric; MPN UNI-ROYAL 0603WAF1001T5E; LCSC C21190
R70, R71, R73: 10k 0.1%; R_0603_1608Metric; MPN YAGEO RT0603BRD0710KL; LCSC C95204
R72: 120k; R_0603_1608Metric; MPN UNI-ROYAL 0603WAF1203T5E; LCSC C25808
R74, R75, R76, R77, R78: 2k2; R_0603_1608Metric; MPN UNI-ROYAL 0603WAF2201T5E; LCSC C4190
R79, R80, R81, R82, R84, R86: 100k; R_0603_1608Metric; MPN UNI-ROYAL 0603WAF1003T5E; LCSC C25803
R83, R85: 100; R_0603_1608Metric; MPN UNI-ROYAL 0603WAF1000T5E; LCSC C22775
RL1, RL2, RL3, RL4, RL5, RL6: 10k; R_0603_1608Metric; MPN UNI-ROYAL 0603WAF1002T5E; LCSC C25804
RL7: 1k; R_0603_1608Metric; MPN UNI-ROYAL 0603WAF1001T5E; LCSC C21190
RS1, RS8: 10m; R_2512_6332Metric; MPN YAGEO PA2512FKE7W0R01E; LCSC C375688
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
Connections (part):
5V_BUS: C16.1, C17.1, R16.1, R17.1, RS8.2, RS9.1, TP3.1, U12.3 (VI)
5V_IN: D2.1 (A1), J2.1, R15.1, RS8.1
24V_BUS: C14.1, C15.1, F8.1, R2.1, R3.1, R5.1, R7.1, R9.1, R11.1, R13.1, RS1.2, RS2.1, RS3.1, RS4.1, RS5.1, RS6.1, RS7.1, TP2.1
24V_IN: D1.1 (A1), J1.1, R1.1, RS1.1, TP1.1
+3V3: C10.1, C11.1, C12.1, C13.1, FB1.1, R19.1, R20.1, R21.1, R22.1, TP4.1, U1.4 (VS), U1.16 (VPU), U2.4 (VS), U2.5 (A0), U2.16 (VPU), U3.4 (VS), U3.16 (VPU), U12.2 (VO)
+3V3_MCU: C40.1, C41.1, C42.1, D10.2 (A), D11.2 (A), D12.2 (A), D13.2 (A), D14.2 (A), FB1.2, J22.1, JP1.2 (B), R60.1, R61.1, R62.1, R70.1, TP5.1, U10.4 (VDD)
ADC_CT1: C35.1, D10.3 (K), R74.2, U10.8 (PA1)
ADC_CT2: C36.1, D11.3 (K), R75.2, U10.15 (PB0)
ADC_CT3: C37.1, D12.3 (K), R76.2, U10.16 (PB1)
ADC_CT4: C38.1, D13.3 (K), R77.2, U10.14 (PA7)
ADC_V: C39.1, D14.3 (K), R78.2, U10.7 (PA0)
CHFAN_F: F3A.1, R8.1, RL3.1, RS4.2
CRITICAL: J10.4, J11.1, R19.2, TP9.1, U1.9 (Critical), U2.9 (Critical), U3.9 (Critical), U10.18 (PA8)
CT1_S: J20.1, R74.1, R79.1
CT2_S: J20.3, R75.1, R80.1
CT3_S: J20.4, R76.1, R81.1
CT4_S: J20.7, R77.1, R82.1
GND: C10.2, C11.2, C12.2, C13.2, C14.2, C15.2, C16.2, C17.2, C30.2, C31.2, C35.2, C36.2, C37.2, C38.2, C39.2, C40.2, C41.2, C42.2, C43.2, D1.2 (A2), D2.2 (A2), D10.1 (K), D11.1 (K), D12.1 (K), D13.1 (K), D14.1 (K), J1.2, J2.2, J3.2, J4.2, J5.2, J6.2, J7.2, J8.2, J9.2, J10.1, J11.2, J20.SH, J22.5, LED10.1 (K), Q2.2 (S), R71.2, R84.2, R86.2, SW1.2, TP10.1, U1.3 (GND), U1.5 (A0), U1.17 (EP), U2.3 (GND), U2.17 (EP), U3.3 (GND), U3.17 (EP), U10.5 (VSS), U12.1 (GND)
HEATER_EN_MCU: R83.1, U10.32 (PB8)
HEATER_EN_PI: J10.6, R85.1
LED_STAT: R65.1, U10.17 (PB2)
LIGHTS_F: F5A.1, R12.1, RL5.1, RS6.2
NEVERMORE_F: F4A.1, R10.1, RL4.1, RS5.2
NRST: C43.1, J22.4, SW1.1, U10.6 (PF2)
unnamed: F1B.1, J3.1, LEDF1.1 (K)
unnamed: F2B.1, J4.1, LEDF2.1 (K)
unnamed: F3B.1, J5.1, LEDF3.1 (K)
unnamed: F4B.1, J6.1, LEDF4.1 (K)
unnamed: F5B.1, J7.1, LEDF5.1 (K)
unnamed: F6B.1, J8.1, LEDF6.1 (K)
unnamed: F7B.1, J9.1, LEDF7.1 (K)
unnamed: J21.1, R72.1
unnamed: JP1.1 (A), R64.2
unnamed: LED10.2 (A), R65.2
unnamed: LED11.2 (A), R87.2
unnamed: LEDF1.2 (A), RL1.2
unnamed: LEDF2.2 (A), RL2.2
unnamed: LEDF3.2 (A), RL3.2
unnamed: LEDF4.2 (A), RL4.2
unnamed: LEDF5.2 (A), RL5.2
unnamed: LEDF6.2 (A), RL6.2
unnamed: LEDF7.2 (A), RL7.2
unnamed: Q1.1 (G), R83.2, R84.1
unnamed: Q2.1 (G), R85.2, R86.1
PA3_RX2: R60.2, U10.10 (PA3)
PA4_NSS: R62.2, U10.11 (PA4)
PA10_RX1: R61.2, U10.21 (PA10/UCPD1_DBCC2)
PI_F: F7A.1, R18.1, RL7.1, RS9.2
RLY_COIL-: D15.2 (A), J12.2, LED11.1 (K), Q1.3 (D)
RLY_MID: Q1.2 (S), Q2.3 (D)
RLY_V+: D15.1 (K), F8.2, J12.1, R87.1
SB2040_F: F2A.1, R6.1, RL2.1, RS3.2
SCL: J10.3, R22.2, TP8.1, U1.6 (SCL), U2.6 (SCL), U3.6 (SCL), U10.30 (PB6)
SDA: J10.2, R21.2, TP7.1, U1.7 (SDA), U2.7 (SDA), U3.5 (A0), U3.7 (SDA), U10.31 (PB7)
SPARE_F: F6A.1, R14.1, RL6.1, RS7.2
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
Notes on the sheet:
INPUTS + PROTECTION
U1 INA3221 @ 0x40 (A0 = GND)
U2 INA3221 @ 0x41 (A0 = +3V3)
U3 INA3221 @ 0x42 (A0 = SDA)
FUSED OUTPUTS - mini blade (ATM) fuse in 2x Keystone 3557 clips; red LED lights when the fuse is blown and a load is connected
F1 10A
F2 5A
F3 3A
F4 3A
F5 3A
F6 3A
F7 5A
3V3 + STM32G071 (mains V/I/W, I2C target 0x50)
Bootloader pins idle high (AN2606 Rev 62 table 91)
JP1 works only after nBOOT_SEL = 0 (factory 1)
MAINS ANALOG - CT board via RJ45 (shielded Cat6) + AC-AC adapter
PI I2C HEADER + ALERTS
TEST POINTS + MOUNTING
HEATER SAFETY RELAY - coil on only if STM32 AND Pi enable (fail-safe, NO contacts)
DESIGN CALCULATIONS - DC side (INA3221, datasheet SBOS576C)
Shunt full scale 163.84 mV, LSB 40 uV, offset 80 uV max. P = I^2 x R. ATM fuse: 1.1x rating may flow indefinitely, 1.35x up to 30 min -> P@1.35xF is the worst case. CH Rsh FS LSB Imax P@Imax P@1.1xF P@1.35xF Vos max U1.1 24V in 10m 16.4A 4.0mA 8.5A 0.72W PSU OCP 11.9A: 1.42W 8.0mA U1.2 Spider 5m 32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
DESIGN CALCULATIONS - mains side + MCU
CT ZMCT103C 1000:1, burden 49.9 ohm (datasheet specs 0.2 %, <=15', 0-15 A linear at 50 ohm). V = I/1000 x 49.9: 6.3 A -> 314 mV, 3.3 A -> 165 mV, 2.2 A -> 110 mV rms. Swing +-1.60 V around 1.65 V -> clips at 1.60/49.9 x 1000/sqrt2 = 22.7 A rms. 1 LSB = 3.3/4096/49.9 x 1000 = 16 mA (3.7 W); RMS over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
